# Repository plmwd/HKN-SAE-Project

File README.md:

# HKN-SAE-Project 2019
A collaboration between UCF's HKN Zeta Chi and SAE club to expand SAE's measurement network for their formula racecar.

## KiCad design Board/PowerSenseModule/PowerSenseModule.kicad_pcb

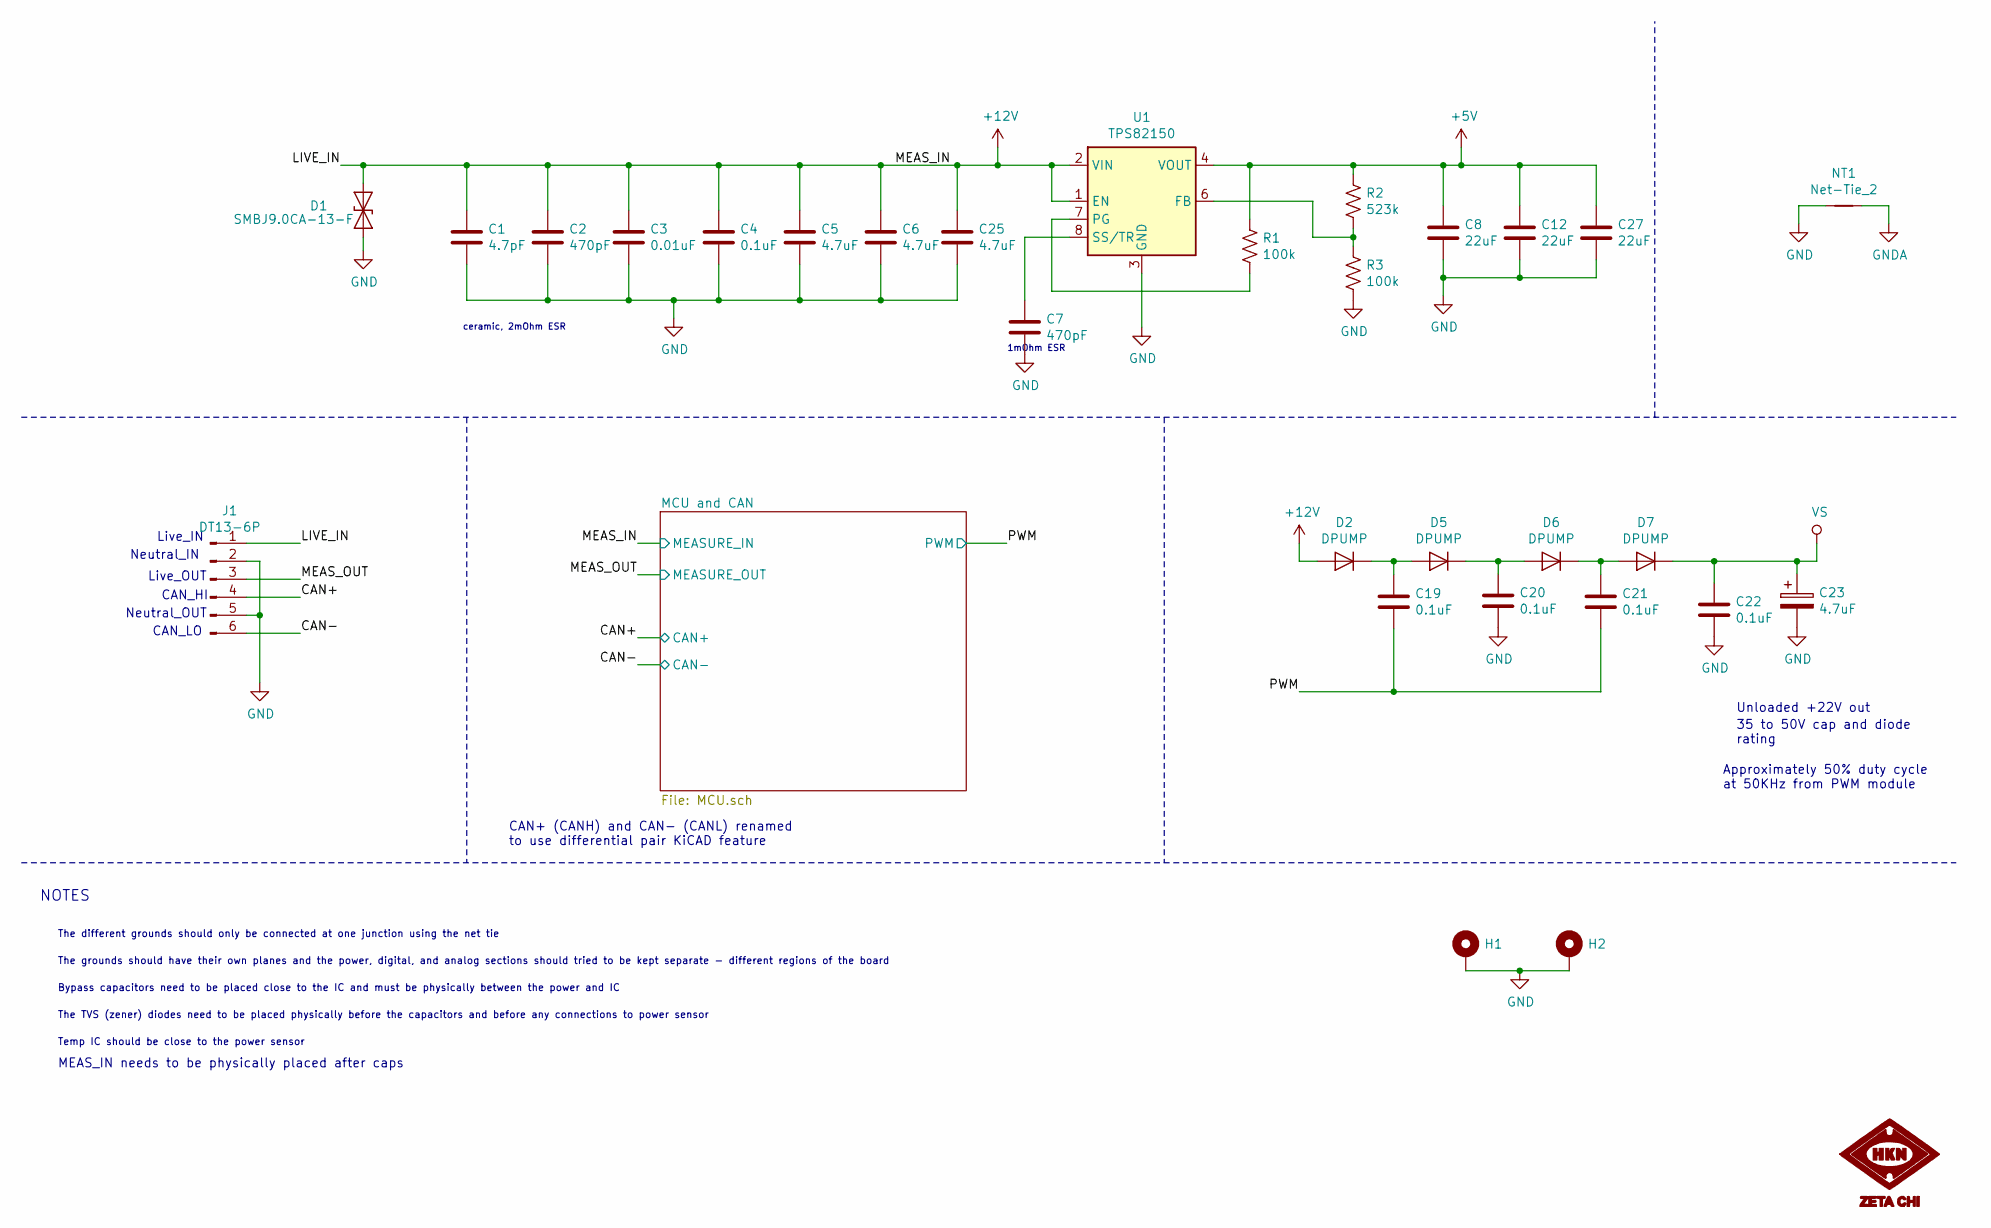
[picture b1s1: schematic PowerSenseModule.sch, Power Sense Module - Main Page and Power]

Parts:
C1: 4.7pF; C_0603_1608Metric_Pad1.05x0.95mm_HandSolder; Manufacturer PN C0603X479C1HACTU
C2, C7: 470pF; C_0603_1608Metric_Pad1.05x0.95mm_HandSolder; Manufacturer PN C0603C471J5GAC7411
C3: 0.01uF; C_0603_1608Metric_Pad1.05x0.95mm_HandSolder; Manufacturer PN C0603C103J5RACTU
C4, C19, C20, C21, C22: 0.1uF; C_0603_1608Metric_Pad1.05x0.95mm_HandSolder; Manufacturer PN CGA3E2X7R1H104K080AA
C5, C6, C23, C25: 4.7uF; C_0805_2012Metric_Pad1.15x1.40mm_HandSolder; Manufacturer PN GRM21BC81H475KE11L
C8, C12, C27: 22uF; C_1210_3225Metric_Pad1.42x2.65mm_HandSolder; Manufacturer PN CL32B226MOJNNNE
D1: SMBJ9.0CA-13-F; D_SMB_Handsoldering; Manufacturer PN SMBJ9.0CA-13-F
D2, D5, D6, D7: DPUMP; D_SOD-323_HandSoldering; Manufacturer PN CUS10S30,H3F
G1: LOGO; HKNZetaChi
H1, H2: MountingHole_2.7mm_M2.5_Pad
J1: DT13-6P; Manufacturer PN DT13-6P
NT1: Net-Tie_2; NetTie-2_SMD_Pad2.0mm
R1, R3: 100k; R_0603_1608Metric_Pad1.05x0.95mm_HandSolder; Manufacturer PN CRCW0603100KFKEA
R2: 523k; R_0603_1608Metric_Pad1.05x0.95mm_HandSolder; Manufacturer PN CR0603-FX-5233ELF
U1: TPS82150; Texas_SIL0008D_MicroSiP-8-1EP_2.8x3mm_P0.65mm_EP1.1x1.9mm; Manufacturer PN TPS82150SILR

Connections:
+5V: C8.1, C12.1, C27.1, R1.1, R2.1, U1.4 (VOUT), U1.5 (VOUT); also elsewhere on the board
+12V: C1.1, C2.1, C3.1, C4.1, C5.1, C6.1, C25.1, D1.1 (A1), D2.2 (A), J1.1, U1.1 (EN), U1.2 (VIN); also elsewhere on the board
/CAN+: J1.4; also elsewhere on the board
/CAN-: J1.6; also elsewhere on the board
/MEAS_OUT: J1.3; also elsewhere on the board
/PWM: C19.2, C21.2; also elsewhere on the board
GND: C1.2, C2.2, C3.2, C4.2, C5.2, C6.2, C7.2, C8.2, C12.2, C20.2, C22.2, C23.2, C25.2, C27.2, D1.2 (A2), H1.1, H2.1, J1.2, J1.5, NT1.1, R3.2, U1.3 (GND), U1.9 (GND); also elsewhere on the board
GNDA: NT1.2; also elsewhere on the board
unnamed: C7.1, U1.8 (SS/TR)
unnamed: C19.1, D2.1 (K), D5.2 (A)
unnamed: C20.1, D5.1 (K), D6.2 (A)
unnamed: C21.1, D6.1 (K), D7.2 (A)
unnamed: R1.2, U1.7 (PG)
unnamed: R2.2, R3.1, U1.6 (FB)
VS: C22.1, C23.1, D7.1 (K); also elsewhere on the board

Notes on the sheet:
Neutral_OUT
Live_OUT
Neutral_IN
Live_IN
NOTES
The grounds should have their own planes and the power, digital, and analog sections should tried to be kept separate - different regions of the board
Bypass capacitors need to be placed close to the IC and must be physically between the power and IC
The TVS (zener) diodes need to be placed physically before the capacitors and before any connections to power sensor
The different grounds should only be connected at one junction using the net tie
Temp IC should be close to the power sensor
1mOhm ESR
ceramic, 2mOhm ESR
CAN_HI
CAN_LO
Unloaded +22V out
35 to 50V cap and diode rating
MEAS_IN needs to be physically placed after caps
Approximately 50% duty cycle at 50KHz from PWM module
CAN+ (CANH) and CAN- (CANL) renamed to use differential pair KiCAD feature

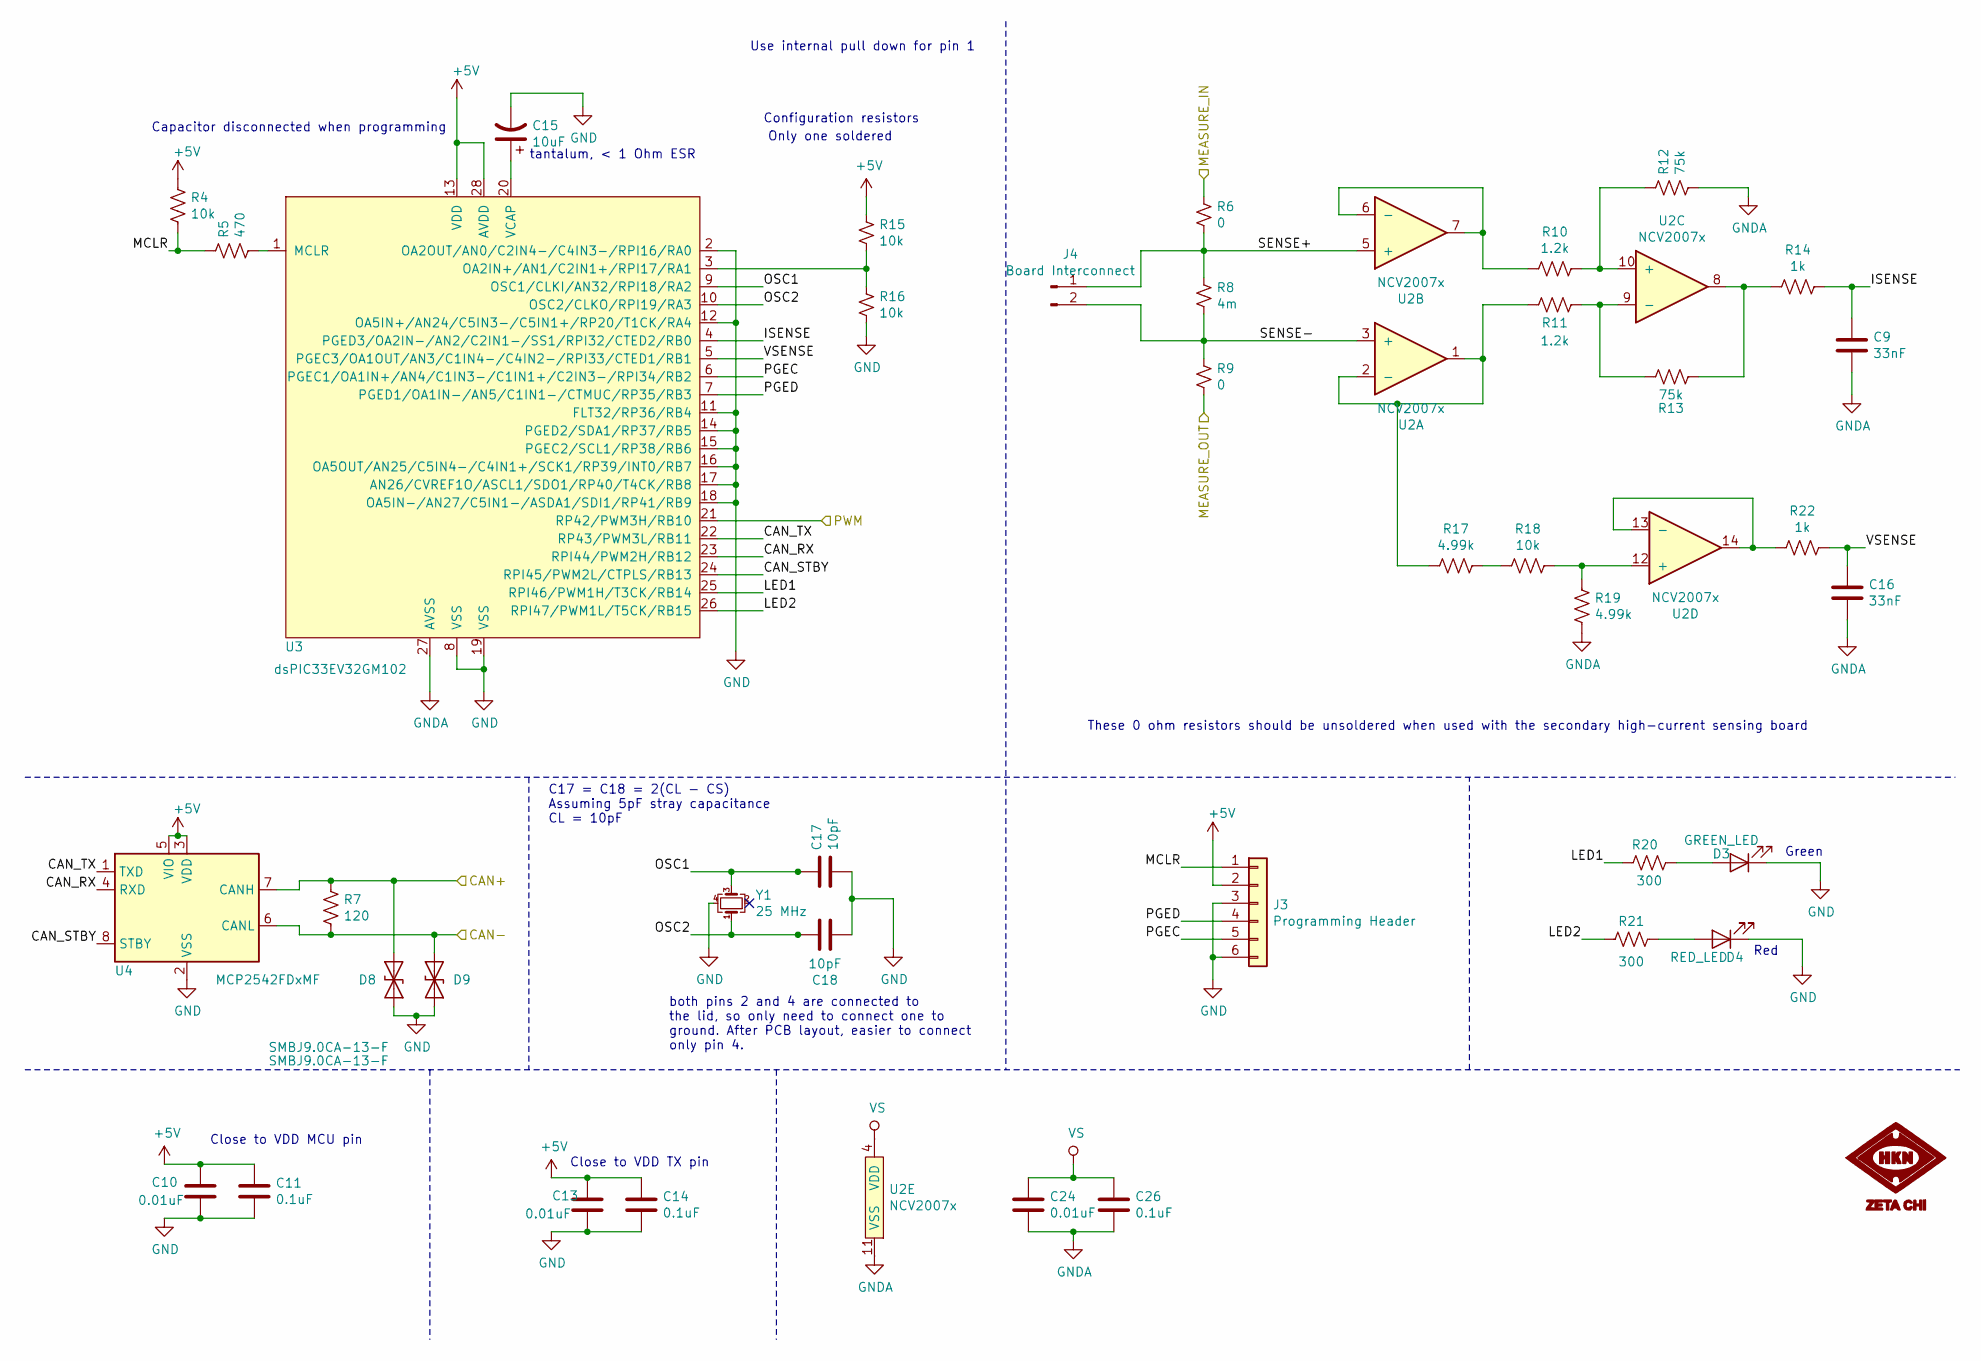
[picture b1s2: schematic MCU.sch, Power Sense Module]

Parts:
C9, C16: 33nF; C_0603_1608Metric_Pad1.05x0.95mm_HandSolder; Manufacturer PN CGA3E2X7R1H333M080AA
C10, C13, C24: 0.01uF; C_0603_1608Metric_Pad1.05x0.95mm_HandSolder; Manufacturer PN C0603C103J5RACTU
C11, C14, C26: 0.1uF; C_0603_1608Metric_Pad1.05x0.95mm_HandSolder; Manufacturer PN CGA3E2X7R1H104K080AA
C15: 10uF; CP_EIA-3528-12_Kemet-T_Pad1.50x2.35mm_HandSolder; Manufacturer PN T491B106K016ATAUTO
C17, C18: 10pF; C_0603_1608Metric_Pad1.05x0.95mm_HandSolder; Manufacturer PN C0603C100J5GAC3190
D3: GREEN_LED; R_0603_1608Metric_Pad1.05x0.95mm_HandSolder; Manufacturer PN 150060VS75000
D4: RED_LED; R_0603_1608Metric_Pad1.05x0.95mm_HandSolder; Manufacturer PN 150060RS75000
D8, D9: SMBJ9.0CA-13-F; D_SMB_Handsoldering; Manufacturer PN SMBJ9.0CA-13-F
J3: Programming Header; PinHeader_1x06_P2.54mm_Vertical
J4: Board Interconnect; PinHeader_1x02_P2.54mm_Vertical
R4, R15, R16, R18: 10k; R_0603_1608Metric_Pad1.05x0.95mm_HandSolder; Manufacturer PN ERJ-PA3J103V
R5: 470; R_0603_1608Metric_Pad1.05x0.95mm_HandSolder; Manufacturer PN ERJ-PA3J471V
R6, R9: 0; R_2816_7142Metric_Pad3.20x4.45mm_HandSolder; Manufacturer PN 5102
R7: 120; R_0603_1608Metric_Pad1.05x0.95mm_HandSolder; Manufacturer PN ERJ-PA3J121V
R8: 4m; R_4020_10251Metric_Pad1.65x5.30mm_HandSolder; Manufacturer PN WSLP39214L000FEB
R10, R11: 1.2k; R_0603_1608Metric_Pad1.05x0.95mm_HandSolder; Manufacturer PN ERJ-PA3J122V
R12, R13: 75k; R_0603_1608Metric_Pad1.05x0.95mm_HandSolder; Manufacturer PN ERJ-PA3J753V
R14, R22: 1k; R_0603_1608Metric_Pad1.05x0.95mm_HandSolder; Manufacturer PN ERJ-PA3J102V
R17, R19: 4.99k; R_0603_1608Metric_Pad1.05x0.95mm_HandSolder; Manufacturer PN RCS06034K99FKEA
R20, R21: 300; R_0603_1608Metric_Pad1.05x0.95mm_HandSolder; Manufacturer PN ERJ-PA3J301V
U2: NCV2007x; SOIC-14_3.9x8.7mm_P1.27mm; Manufacturer PN NCV20074DR2G
U3: dsPIC33EV32GM102; SSOP-28_5.3x10.2mm_P0.65mm; Manufacturer PN dsPIC33EV32GM102-E/SS
U4: MCP2542FDxMF; SOIC-8_3.9x4.9mm_P1.27mm; Manufacturer PN MCP2542FD-H/SN
Y1: 25 MHz; Crystal_SMD_S2.05mm_L2.55; Manufacturer PN ABM10AIG-25.000MHZ-4Z-T3

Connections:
+5V: C10.1, C11.1, C13.1, C14.1, J3.2, R4.1, R15.1, U3.13 (VDD), U3.28 (AVDD), U4.3 (VDD), U4.5 (VIO); also elsewhere on the board
+12V: R6.1; also elsewhere on the board
/CAN+: D8.1 (A1), R7.1, U4.7 (CANH); also elsewhere on the board
/CAN-: D9.1 (A1), R7.2, U4.6 (CANL); also elsewhere on the board
/MCU and CAN/CAN_RX: U3.23 (RPI44/PWM2H/RB12), U4.4 (RXD)
/MCU and CAN/CAN_STBY: U3.24 (RPI45/PWM2L/CTPLS/RB13), U4.8 (STBY)
/MCU and CAN/CAN_TX: U3.22 (RP43/PWM3L/RB11), U4.1 (TXD)
/MCU and CAN/ISENSE: C9.1, R14.1, U3.4 (PGED3/OA2IN-/AN2/C2IN1-/SS1/RPI32/CTED2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)
/MCU and CAN/LED1: R20.2, U3.25 (RPI46/PWM1H/T3CK/RB14)
/MCU and CAN/LED2: R21.2, U3.26 (RPI47/PWM1L/T5CK/RB15)
/MCU and CAN/MCLR: J3.1, R4.2, R5.1
/MCU and CAN/OSC1: C17.1, U3.9 (OSC1/CLKI/AN32/RPI18/RA2), Y1.3
/MCU and CAN/OSC2: C18.1, U3.10 (OSC2/CLKO/RPI19/RA3), Y1.1
/MCU and CAN/PGEC: J3.5, U3.6 (PGEC1/OA1IN+/AN4/C1IN3-/C1IN1+/C2IN3-/R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)
/MCU and CAN/PGED: J3.4, U3.7 (PGED1/OA1IN-/AN5/C1IN1-/CTMUC/RP35/RB3)
/MCU and CAN/SENSE+: J4.1, R6.2, R8.1, U2.5 (+)
/MCU and CAN/SENSE-: J4.2, R8.2, R9.1, U2.3 (+)
/MCU and CAN/VSENSE: C16.1, R22.1, U3.5 (PGEC3/OA1OUT/AN3/C1IN4-/C4IN2-/RPI33/CT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)
/MEAS_OUT: R9.2; also elsewhere on the board
/PWM: U3.21 (RP42/PWM3H/RB10); also elsewhere on the board
GND: C10.2, C11.2, C13.2, C14.2, C15.2, C17.2, C18.2, D3.1 (K), D4.1 (K), D8.2 (A2), D9.2 (A2), J3.3, J3.6, R16.2, U3.2 (OA2OUT/AN0/C2IN4-/C4IN3-/RPI16/RA0), U3.8 (VSS), U3.11 (FLT32/RP36/RB4), U3.12 (OA5IN+/AN24/C5IN3-/C5IN1+/RP20/T1CK/RA4), U3.14 (PGED2/SDA1/RP37/RB5), U3.15 (PGEC2/SCL1/RP38/RB6), U3.16 (OA5OUT/AN25/C5IN4-/C4IN1+/SCK1/RP39/INT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), U3.17 (AN26/CVREF1O/ASCL1/SDO1/RP40/T4CK/RB8), U3.18 (OA5IN-/AN27/C5IN1-/ASDA1/SDI1/RP41/RB9), U3.19 (VSS), U4.2 (VSS), U4.9 (VSS), Y1.4; also elsewhere on the board
GNDA: C9.2, C16.2, C24.2, C26.2, R12.2, R19.1, U2.11 (VSS), U3.27 (AVSS); also elsewhere on the board
unnamed: C15.1, U3.20 (VCAP)
unnamed: D3.2 (A), R20.1
unnamed: D4.2 (A), R21.1
unnamed: R5.2, U3.1 (MCLR)
unnamed: R10.1, R12.1, U2.10 (+)
unnamed: R10.2, U2.6 (-), U2.7
unnamed: R11.1, R13.2, U2.9 (-)
unnamed: R11.2, R17.2, U2.1, U2.2 (-)
unnamed: R13.1, R14.2, U2.8
unnamed: R15.2, R16.1, U3.3 (OA2IN+/AN1/C2IN1+/RPI17/RA1)
unnamed: R17.1, R18.2
unnamed: R18.1, R19.2, U2.12 (+)
unnamed: R22.2, U2.13 (-), U2.14
VS: C24.1, C26.1, U2.4 (VDD); also elsewhere on the board

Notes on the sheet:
Close to VDD TX pin
Close to VDD MCU pin
Green
Red
These 0 ohm resistors should be unsoldered when used with the secondary high-current sensing board
both pins 2 and 4 are connected to the lid, so only need to connect one to ground. After PCB layout, easier to connect only pin 4.
C17 = C18 = 2(CL - CS) Assuming 5pF stray capacitance CL = 10pF
Capacitor disconnected when programming
tantalum, < 1 Ohm ESR
Only one soldered
Configuration resistors
Use internal pull down for pin 1

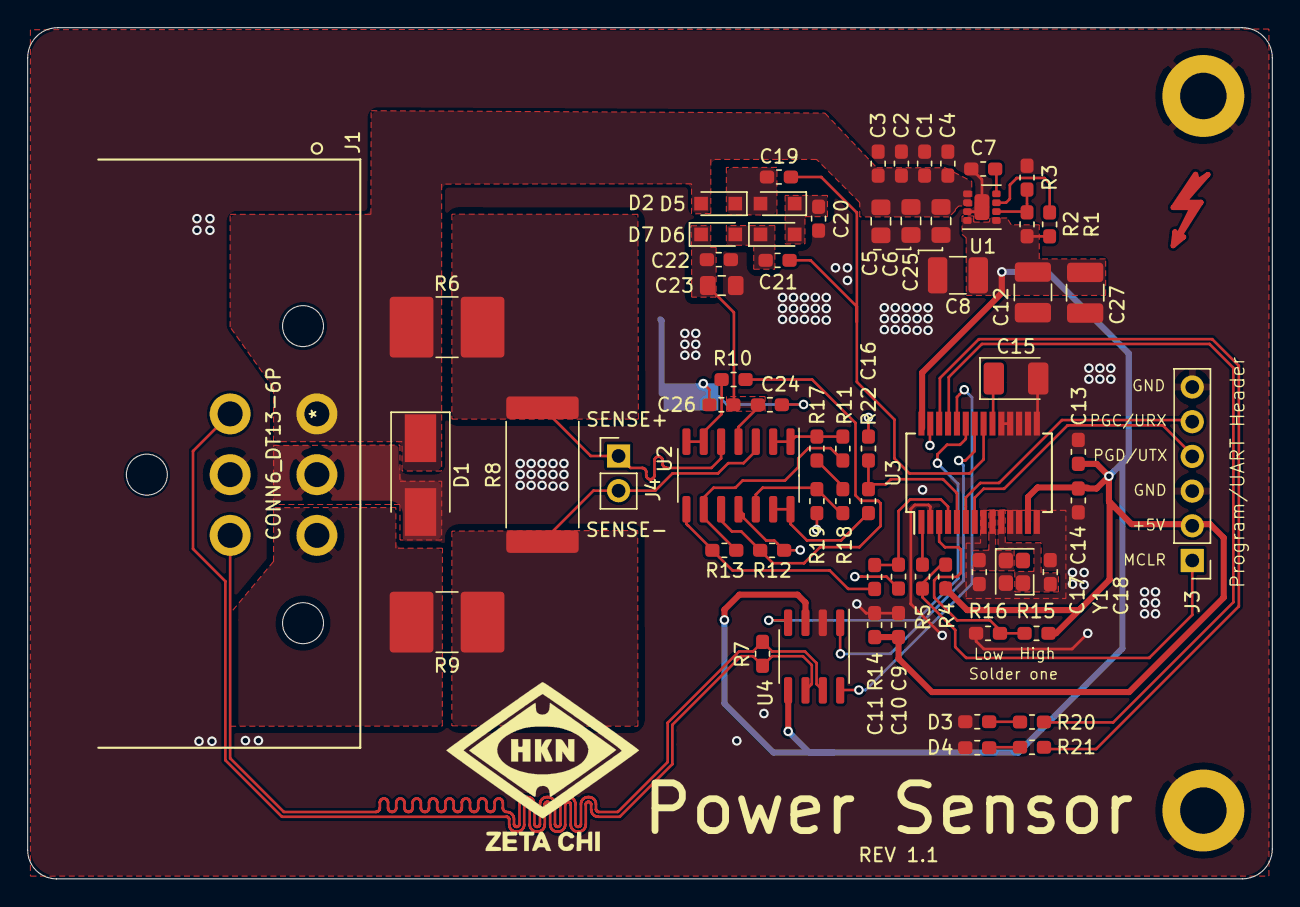
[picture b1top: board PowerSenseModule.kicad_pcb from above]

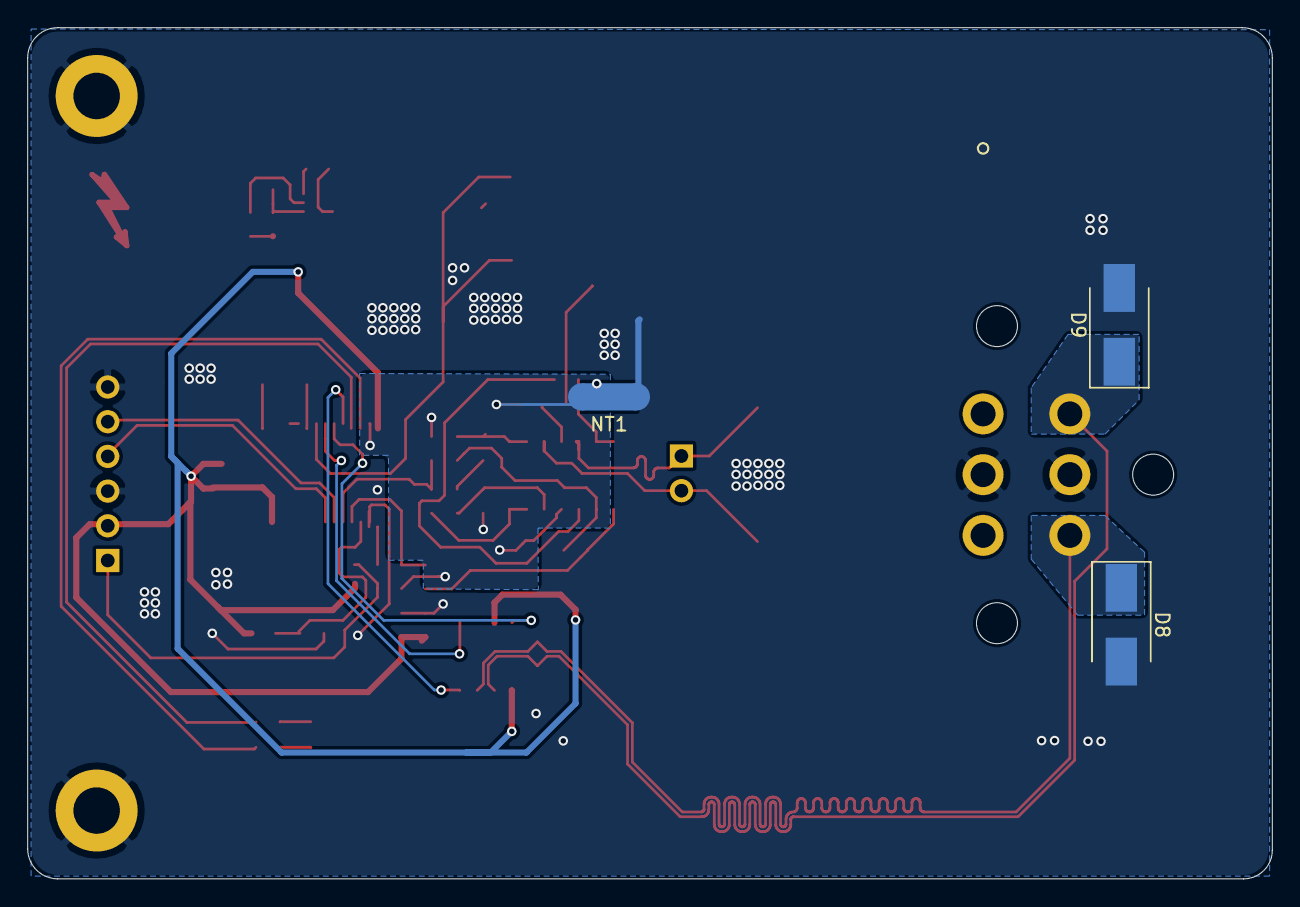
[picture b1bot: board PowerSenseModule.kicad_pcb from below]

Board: 2 copper layers, 91.1 x 62.3 mm, 71 parts (3 on the bottom side), 42 nets.

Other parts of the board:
Danger: Symbol_Highvoltage_Type1_CopperTop_Small

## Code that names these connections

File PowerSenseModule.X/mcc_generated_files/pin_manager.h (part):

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*/
/**
  @Summary
    Sets the GPIO pin, RA0, high using LATA0.

  @Description
    Sets the GPIO pin, RA0, high using LATA0.

  @Preconditions
    The RA0 must be set to an output.
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#define DCME_SetHigh()          _LATA0 = 1
/**
  @Summary
    Sets the GPIO pin, RA0, low using LATA0.

  @Description
    Sets the GPIO pin, RA0, low using LATA0.

  @Preconditions
    The RA0 must be set to an output.
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#define DCME_SetLow()           _LATA0 = 0
/**
  @Summary
    Toggles the GPIO pin, RA0, using LATA0.

  @Description
    Toggles the GPIO pin, RA0, using LATA0.

  @Preconditions
    The RA0 must be set to an output.
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#define DCME_Toggle()           _LATA0 ^= 1
/**
  @Summary
    Reads the value of the GPIO pin, RA0.

  @Description
    Reads the value of the GPIO pin, RA0.

  @Preconditions
    None.
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    </code>

*/
#define DCME_GetValue()         _RA0
/**
  @Summary
    Configures the GPIO pin, RA0, as an input.

  @Description
    Configures the GPIO pin, RA0, as an input.

  @Preconditions
    None.
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#define DCME_SetDigitalInput()  _TRISA0 = 1
/**
  @Summary
    Configures the GPIO pin, RA0, as an output.

  @Description
    Configures the GPIO pin, RA0, as an output.

  @Preconditions
    None.
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#define DCME_SetDigitalOutput() _TRISA0 = 0
/**
  @Summary
    Sets the GPIO pin, RA1, high using LATA1.

  @Description
    Sets the GPIO pin, RA1, high using LATA1.

  @Preconditions
    The RA1 must be set to an output.
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#define HIGH_IE_SetHigh()          _LATA1 = 1
/**
  @Summary
    Sets the GPIO pin, RA1, low using LATA1.

  @Description
    Sets the GPIO pin, RA1, low using LATA1.

  @Preconditions
    The RA1 must be set to an output.
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#define HIGH_IE_SetLow()           _LATA1 = 0
/**
  @Summary
    Toggles the GPIO pin, RA1, using LATA1.

  @Description
    Toggles the GPIO pin, RA1, using LATA1.

  @Preconditions
    The RA1 must be set to an output.
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#define HIGH_IE_Toggle()           _LATA1 ^= 1
/**
  @Summary
    Reads the value of the GPIO pin, RA1.

  @Description
    Reads the value of the GPIO pin, RA1.

  @Preconditions
    None.
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    </code>

*/
#define HIGH_IE_GetValue()         _RA1
/**
  @Summary
    Configures the GPIO pin, RA1, as an input.

  @Description
    Configures the GPIO pin, RA1, as an input.

  @Preconditions
    None.
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#define HIGH_IE_SetDigitalInput()  _TRISA1 = 1
/**
  @Summary
    Configures the GPIO pin, RA1, as an output.

  @Description
    Configures the GPIO pin, RA1, as an output.

  @Preconditions
    None.
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#define HIGH_IE_SetDigitalOutput() _TRISA1 = 0
/**
  @Summary
    Sets the GPIO pin, RB11, high using LATB11.

  @Description
    Sets the GPIO pin, RB11, high using LATB11.

  @Preconditions
    The RB11 must be set to an output.
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#define CAN_TX_SetHigh()          _LATB11 = 1
/**
  @Summary
    Sets the GPIO pin, RB11, low using LATB11.

  @Description
    Sets the GPIO pin, RB11, low using LATB11.

  @Preconditions
    The RB11 must be set to an output.
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#define CAN_TX_SetLow()           _LATB11 = 0
/**
  @Summary
    Toggles the GPIO pin, RB11, using LATB11.

  @Description
    Toggles the GPIO pin, RB11, using LATB11.

  @Preconditions
    The RB11 must be set to an output.
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#define CAN_TX_Toggle()           _LATB11 ^= 1
/**
  @Summary
    Reads the value of the GPIO pin, RB11.

  @Description
    Reads the value of the GPIO pin, RB11.

  @Preconditions
    None.
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    </code>

*/
#define CAN_TX_GetValue()         _RB11
/**
  @Summary
    Configures the GPIO pin, RB11, as an input.

  @Description
    Configures the GPIO pin, RB11, as an input.

  @Preconditions
    None.
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#define CAN_TX_SetDigitalInput()  _TRISB11 = 1
/**
  @Summary
    Configures the GPIO pin, RB11, as an output.

  @Description
    Configures the GPIO pin, RB11, as an output.

  @Preconditions
    None.
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#define CAN_TX_SetDigitalOutput() _TRISB11 = 0
/**
  @Summary
    Sets the GPIO pin, RB12, high using LATB12.

  @Description
    Sets the GPIO pin, RB12, high using LATB12.

  @Preconditions
    The RB12 must be set to an output.
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#define CAN_RX_SetHigh()          _LATB12 = 1
/**
  @Summary
    Sets the GPIO pin, RB12, low using LATB12.

  @Description
    Sets the GPIO pin, RB12, low using LATB12.

  @Preconditions
    The RB12 must be set to an output.
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#define CAN_RX_SetLow()           _LATB12 = 0
/**
  @Summary
    Toggles the GPIO pin, RB12, using LATB12.

  @Description
    Toggles the GPIO pin, RB12, using LATB12.

  @Preconditions
    The RB12 must be set to an output.
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#define CAN_RX_Toggle()           _LATB12 ^= 1
/**
  @Summary
    Reads the value of the GPIO pin, RB12.

  @Description
    Reads the value of the GPIO pin, RB12.

  @Preconditions
    None.
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    </code>

*/
#define CAN_RX_GetValue()         _RB12
/**
  @Summary
    Configures the GPIO pin, RB12, as an input.

  @Description
    Configures the GPIO pin, RB12, as an input.

  @Preconditions
    None.
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#define CAN_RX_SetDigitalInput()  _TRISB12 = 1
/**
  @Summary
    Configures the GPIO pin, RB12, as an output.

  @Description
    Configures the GPIO pin, RB12, as an output.

  @Preconditions
    None.
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#define CAN_RX_SetDigitalOutput() _TRISB12 = 0
/**
  @Summary
    Sets the GPIO pin, RB13, high using LATB13.

  @Description
    Sets the GPIO pin, RB13, high using LATB13.

  @Preconditions
    The RB13 must be set to an output.
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#define CAN_STBY_SetHigh()          _LATB13 = 1
/**
  @Summary
    Sets the GPIO pin, RB13, low using LATB13.

  @Description
    Sets the GPIO pin, RB13, low using LATB13.

  @Preconditions
    The RB13 must be set to an output.
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#define CAN_STBY_SetLow()           _LATB13 = 0
/**
  @Summary
    Toggles the GPIO pin, RB13, using LATB13.

  @Description
    Toggles the GPIO pin, RB13, using LATB13.

  @Preconditions
    The RB13 must be set to an output.
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#define CAN_STBY_Toggle()           _LATB13 ^= 1
/**
  @Summary
    Reads the value of the GPIO pin, RB13.

  @Description
    Reads the value of the GPIO pin, RB13.

  @Preconditions
    None.
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    </code>

*/
#define CAN_STBY_GetValue()         _RB13
/**
  @Summary
    Configures the GPIO pin, RB13, as an input.

  @Description
    Configures the GPIO pin, RB13, as an input.

  @Preconditions
    None.
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#define CAN_STBY_SetDigitalInput()  _TRISB13 = 1
/**
  @Summary
    Configures the GPIO pin, RB13, as an output.

  @Description
    Configures the GPIO pin, RB13, as an output.

  @Preconditions
    None.
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#define CAN_STBY_SetDigitalOutput() _TRISB13 = 0
/**
  @Summary
    Sets the GPIO pin, RB14, high using LATB14.

  @Description
    Sets the GPIO pin, RB14, high using LATB14.

  @Preconditions
    The RB14 must be set to an output.
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#define LED_R_SetHigh()          _LATB14 = 1
/**
  @Summary
    Sets the GPIO pin, RB14, low using LATB14.

  @Description
    Sets the GPIO pin, RB14, low using LATB14.

  @Preconditions
    The RB14 must be set to an output.
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#define LED_R_SetLow()           _LATB14 = 0
/**
  @Summary
    Toggles the GPIO pin, RB14, using LATB14.

  @Description
    Toggles the GPIO pin, RB14, using LATB14.

  @Preconditions
    The RB14 must be set to an output.
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#define LED_R_Toggle()           _LATB14 ^= 1
/**
  @Summary
    Reads the value of the GPIO pin, RB14.

  @Description
    Reads the value of the GPIO pin, RB14.

  @Preconditions
    None.
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    </code>

*/
#define LED_R_GetValue()         _RB14
/**
  @Summary
    Configures the GPIO pin, RB14, as an input.

  @Description
    Configures the GPIO pin, RB14, as an input.

  @Preconditions
    None.
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#define LED_R_SetDigitalInput()  _TRISB14 = 1
/**
  @Summary
    Configures the GPIO pin, RB14, as an output.

  @Description
    Configures the GPIO pin, RB14, as an output.

  @Preconditions
    None.
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#define LED_R_SetDigitalOutput() _TRISB14 = 0
/**
  @Summary
    Sets the GPIO pin, RB15, high using LATB15.

  @Description
    Sets the GPIO pin, RB15, high using LATB15.

  @Preconditions
    The RB15 must be set to an output.
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#define LED_G_SetHigh()          _LATB15 = 1
/**
  @Summary
    Sets the GPIO pin, RB15, low using LATB15.

  @Description
    Sets the GPIO pin, RB15, low using LATB15.

  @Preconditions
    The RB15 must be set to an output.
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#define LED_G_SetLow()           _LATB15 = 0
/**
  @Summary
    Toggles the GPIO pin, RB15, using LATB15.

  @Description
    Toggles the GPIO pin, RB15, using LATB15.

  @Preconditions
    The RB15 must be set to an output.
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#define LED_G_Toggle()           _LATB15 ^= 1
/**
  @Summary
    Reads the value of the GPIO pin, RB15.

  @Description
    Reads the value of the GPIO pin, RB15.

  @Preconditions
    None.
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    </code>

*/
#define LED_G_GetValue()         _RB15
/**
  @Summary
    Configures the GPIO pin, RB15, as an input.

  @Description
    Configures the GPIO pin, RB15, as an input.

  @Preconditions
    None.
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#define LED_G_SetDigitalInput()  _TRISB15 = 1
/**
  @Summary
    Configures the GPIO pin, RB15, as an output.

  @Description
    Configures the GPIO pin, RB15, as an output.

  @Preconditions
    None.
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*/
#define LED_G_SetDigitalOutput() _TRISB15 = 0

#define IIN_ANALOG_INPUT      2       // RB0, AN2
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
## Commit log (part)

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2019-06-24 Created MCU circuit KiCAD project
2019-07-01 KiCAD Project
    Created KiCAD project and created symbols for the dsPIC33EP32GP502 (schematic) for the QFN and SSOP and SOIC package.
2019-07-03 Organized and set footprints
    Organized schematic page (title, company) and added footprints for all parts besides the passives
2019-07-03 Previous push
2019-07-04 Addc global nets to CPU
    Added global nets to CPU for the power sensor IC
    - events 1 and 2
    - adc reset and mclr (need to add pull-up resistors)
    - zero crossing
2019-07-05 Buck Converter design - all that's needed is resistor placement which can be derived from powerbench and wiring for the regulator and output.
2019-07-05 Some cache update?
2019-07-07 Created power sensor circuit
    ADC filter:
    RC chosen so that fc ~= 8KHz (998k and 12p)
    ADC voltage divider:
    30V -> 1V
    10V -> 0.333
    24 bit adc provides 59.6nV/bit - adequate room
2019-07-07 Changed adc filters
    Changed adc filters to have a cutoff close to 50KHz so that the attenuation at 500-1000Hz is 0.98 to 0.99.
    Voltage adc:
    Reff = 33.63K - > C = 820pF
    Current adc:
    R = 1K -> C = 3nF
2019-07-07 Merged branches and organized
    Merged Sensing, MCU, and Power branches to now use GITFlow. Merged schematics to new KiCAD project where now the schematics are hierarchical.
    Fixed MCLR and RST pins for MCP39F511A.
2019-07-11 Verifying credentials
    Please ignore
2019-07-11 Updated .gitignore
2019-07-11 Revert "Modified C file. Added function prototypes"
2019-07-11 Removed rescue lib reference
2019-07-11 Changed power connector and added CAN nets
2019-07-18 include .lib
2019-07-19 Buck
2019-07-20 Added linear reg, cleaned up schematic
2019-07-20 Updated footprints for resistors and caps`
    Chose 0603 hand solder footprints for R and C.
    Need choose footprint for the inductor, connectors, test points, programmer header, and jumper
2019-07-20 Finalizing footprints - a
    Changed footprints of 4.7u, 10u, 47u ceramic caps to 0805 from 0603.
    Changed output cap of linear reg to 150u electrolytic
    Added tie net for grounds
    Connector footprints
    Added notes
    TODO:
2019-07-20 Changed C10 from tantalum to ceramic
2019-07-21 Changed R8 to be a 4 pin shunt resistor
2019-07-21 Changed can interface lib
2019-07-28 Selected parts in BOM
2019-07-28 Started design change
    Changing MCU to 5V dspic33ev32gm102
2019-08-04 Added/Changed footprints
2019-08-06 Moses's changes, removed MPLAB proj
2019-08-06 Merged power and CAN connectors to one connector
2019-08-06 BASE/REFERENCE
    Initial Design.
2019-08-06 closed MPLAB
2019-08-06 Rewiring - of MCU
    Rewired the MCU
2019-08-07 Wrote basic framework
    Removed CAN MCC module (for now).
    Configured ADC for CH0 and CH1 simultaneous sampling, sequential conversion. Generates interrupt after 16 samples (8 samples per channel) - doesn't yet use DMA. Wrote basic main loop and ADC interrup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
    TODO:
    calibration function
    CAN functions and configuration
    TESTING
2019-08-07 Added 'process_x' functions
2019-08-07 Added calibration.h and added some documentation
2019-08-08 edited .gitignore, calibration.h documentation refactor
2019-08-09 Added to PCB layout - Configurations Resistor / PIN 3 mapping
    More of the PCB is laid out. Some mapping remains. Aside from that, what's left is the following,
    - Assuring PCB traces meet current limitations
    - Design review for optimizations for redesign.
    Alongside that, the configuration resistors do not seem to be connected to PIN 3 on the MCU.
2019-08-10 Extra to last commit
2019-08-11 Trying to debug ISR being called twice
2019-08-12 Finally have simultaneous 2 channel sampling
    MPLAB 5.05 works the best
2019-08-12 Redesign/Configuration Resistors Fixed
    Dimensions for PCB defined, might need to be extended for mounting. Rewiring being done to fit dimensions.
2019-08-13 Redesign - Everything up top
    This redesign has all components on top layer. Tracing is all that's left, along side labeling.
2019-08-16 Added globals.h to move buffer declarations
2019-08-22 Changed data types of current and voltage variables/arrays in main to double
2019-08-22 Started CAN init - TX
    CAN init TODO:
    RX - don't know what we would be receiving & filter
    DMA
    Bit timing
    CAN TODO:
    message struct
2019-08-22 OP amp circuit changes
    Move D op amp to voltage sensing
    Changed voltage divider resistors to smaller values
    Changed error in differential amp resistor values (gain)
    Changed error in resistors have capacitor footprints
    Added datasheet link for the op amps
2019-08-24 CAN TX writing to buffer
    Added function to be able to write data of any data type to the data fields in a CAN TX buffer.
    I think the initialization is correct but needs testing.
    Added struct for a CAN message.
    Changed variable type of buffers in global.h.
    Need to write transmit function and test.
2019-08-24 Tested CAN_WriteBuf and edited .gitignore
2019-08-25 Configured DMA for CAN TX and RX
2019-08-25 DMA small changes - need to refactor
2019-08-25 Added more documentation and empty CAN interrupt ISRs
2019-08-26 Finished processVoltage and processCurrent
2019-08-29 misc changes - CAN not transmitting
2019-09-04 Got CAN to transmit
    CAN now transmits correct data, but on Waveforms, I get CRC errors. Also, Unless I clear the request bit, the message will be repeatedly sent unto eternity because of a invalid CAN message error - ne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
    Refactored some DMA code, including adding channel enable/disable functions
2019-09-07 Finished prototype of CalibrateData. Changed return type to double as well as data type of data to double. Changed all member variables of cal_point_t structure to doubles from unsigned int
2019-09-11 Every component wired.
    Each component is wired. I've now decided to make this PCB symmetric though.
2019-09-13 Finished device config - next test
2019-09-13 started UART config
2019-12-10 Updated symbol fields and changed CAN transceiver package to make it easier to solder
2019-12-10 Changed global nets to local nets in MCU page
2019-12-10 Annotated new symbols
2019-12-11 Added info in symbol fields for diodes
2019-12-11 PCB update
    - Laid out buck converter
    - Laid out TE connector, TVS diode, and power sense resistor
    - Created footprint for 4-pin crystal
    - Updated crystal symbol
    - Fixed design rules
    - Moses's PCB design file name appended with *_backup
2019-12-12 Adjusted copper fill zones
2019-12-12 Changed crystal gnd net and working on layout
2019-12-12 layout 0.01
2019-12-12 layout 0.03
2019-12-13 layout 0.04
    - Added top and bottom ground plane
    - changed GNDD to GND
    - readjusted spacing between components
    - made the board a little smaller
    - fine tuned copper fills
    - got pretty good power rail and ground layout
2019-12-14 layout 0.05
    - differential pair for CAN bus
    - differential pair for shunt resistor
2019-12-14 misc
    IDK what changes I did but there were some after saving before closing KiCAD
2019-12-15 layout 1.01
    - Changed 5V traces from 0.2mm to 0.45mm to handle at least 1A
2019-12-15 laylout 1.02
    adjusted 5V traces
2019-12-21 Created BOM
    BOM was created by adding symbol fields then using the KiCAD BOM Wizard plugin
    https://hackaday.io/project/20765-kicad-bom-wizard
    Then the CSV data was imported into Excel and was tweaked.
    Price per unit is about $35-40
2019-12-22 Updated BOM, schematic, PCB
    - Using 3 pin jumper for program enable so that the jumper can be stored on the board
    - Updated footprint for 4.7uF cap from electrolytic to smd 0805
    - cleaned up some copper zones
2019-12-28 Prepped branch for reorganization
    - removed adc, tmr1, tmr3 files
    - renamed dma -> dma_backup
    - renamed main -> main_backup
    - commented out main
2019-12-28 Added files to project
    - added backup files from Firmware branch merge
    - remove uart (not uart1) files from Firmware branch
2019-12-28 Fixed conflicts with merge
    - Lots of things are broken, but testing individual peripherals before fixing main system software
    - Use #define in "device_configuration" file for debug main functions
2019-12-28 Updated gitignore to ignore .mk
2019-12-28 MPLAB added adc and tmr files
2019-12-28 Updated system config
2019-12-28 Made uart change baud rate based off frequency
2019-12-29 Modified uart1 test file to implement sending and receiving through UART. Tested to work both sending and receiving
2019-12-31 Started rewritting ADC firmware to support manual and automatic sampling
2020-01-02 Started implementation for multichannel sampling
    - Need to rethink how to deal with reading ADC buffers
2020-01-02 Figured out how to process ADC buffer for multiple channels
    using cascaded switch statement to only modify channel buffers depending on the channel mode
2020-01-03 Tested multichannel sampling functions
    - multichannel sampling works perfectly
    - Reversed argument order for ADC1_SampleChannels function
    - Added check in ADC1_setPrecision function to force the precision to be 10 bits if the channel mode is dual or multi channel - restriction of the dsPIC
2020-01-04 Verified PGC and PGD dual functionality
    - Verified that the programmer clock and data pins can be used as regular GPIO/other functionalities when the programmer is not plugged in.
2020-01-05 Tested PPS on PGD/C pins
    - Don't need to do anything special to have PPS work along side the programming data and clock pins. They can share the pins and if the programmer is connected, then it takes precedence. Since only o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
2020-01-05 Started refactor of CAN and DMA code
    - untested
    - refactored CAN code to allow for a single function to send data rather than some convoluted series of functions
2020-01-06 Fixed some bugs - not transmitting
    - fixed bug checking for SID bounds where the number wasnt 2^11
    - fixed bug where the WriteTXBuffer() function was starting at the beginning of the CAN message, not where the beginning of the data section is in the message
    - The CAN message doesnt appear on the pin. Could be DMA config or something else with initiating the transfer
2020-01-10 pop stash - weird merge issues with PCB
2020-01-10 Added next rev notes
2020-01-11 Wrote system test for op amp and ADC
    - added "power_sense_module" header and source file for ADC reading conversion from integer value to double current and voltages
    - wrote main function to test op amp and ADC
    - forgot to first implement the PWM module to get a higher op amp VDD
2020-01-12 PCB rev 1.10
    >See GitHub issue for changes:
    https://github.com/paulwood15/HKN-SAE-Project/issues/16
    > Need to update BOM and do design review
2020-01-13 Added TI WebBench design report
2020-01-15 Added timer interrupt code to data_menu.c
2020-01-15 Menu interface is completed
2020-01-18 Updated inventory
2020-01-18 Changed path for HKN logo to be relative to "${CUSTOM_SYMBOL_DIR}"
2020-01-19 Added drawings dimensions, changed footprint of op amp, and cleaned up
2020-01-19 Generated new gerber files just to be sure
2020-01-22 Made final changes to PCB
    - cleaned up vias
    - rounded edges
    - adjusted copper fills
    - ? dont remember what else - only minor, minor changes
2020-01-25 Updated BOM, got prices from suppliers

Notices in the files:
PowerSenseModule.X/mcc_generated_files/pin_manager.h:
(c) 2016 Microchip Technology Inc. and its subsidiaries. You may use this
